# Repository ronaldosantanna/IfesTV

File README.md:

# IfesTV
### Esta Branch é exclusiva do IFES. Os arquivos aqui serão os mesmos da TV presente no IFES.
IfesTV é um site local, no estilo _kiosk_ (Raspberry pi ligado a TV), que exibe videos do youtube, notícias, avisos locais, clima e temperatura ambiente.

> Criado por alunos do IFES - Campus Guarapari. Pelos alunos João Alves, Kevyn Marins e Ronaldo Sant'Anna. [Contato](https://github.com/ronaldosantanna/IfesTV#qualquer-dúvida-ou-sugestão-fiquem-a-vontade)

Utilizamos uma ESP8266 para ligar o sensor local de temperatura DHT11, no qual serve para uma estação remota via comunicalção MQTT com o raspberry pi.
Desse jeito, a raspberry ligada a TV recebe informações de um ou vários sensores em um ou mais prédios e também informações da internet e exibe na TV.

Toda a configuração foi pesquisada na internet e aplicada para este projeto. Aqui tentaremos juntar todas as informações necessárias para a configuração do projeto.

A imagem do sistema já está completa e configurada para uso.

## Hardware
* Raspberry pi 3B + Raspbian [(Img do sistema)](https://drive.google.com/open?id=16IvTq7KXVeJWATDrFhQsSftASu8AablH)
* Esp8266 + [Mosquitto MQTT Server](https://randomnerdtutorials.com/how-to-install-mosquitto-broker-on-raspberry-pi/)
* DHT11

## Configuração do site
O site foi básico apenas para exibir o necessário em nosso projeto. Acima temos os arquivos da página e suas dependencias.
Para editá-lo é simples e qualquer pesquisa na internet já se encontra o passo a passo da criação.

> Para alterar seu conteúdo, por enquanto, temos que acessá-lo remotamente e alterar o valor dentro de seus arquivos de configuração. NO IFES O UNICO LOCAL COM ACESSO REMOTO É A SALA B-307 OU O PRÓPRIO TI.
> 1. Para isso vamos conectar via terminal (pelo linux), ou [Putty](https://the.earth.li/~sgtatham/putty/latest/w32/putty.exe) (windows,   mas teste se seu computador não tem ssh, acessando o cmd e digitando ssh).
 Primeiro devemos descobrir o endereço ip da raspberry. No IFES fixamos o IP dela para 172.17.22.188.
> 2. Conectando pelo hostname fica `ssh pi@172.17.22.188` 
> 3. No terminal digitamos a senha.
 Agora vamos modificar o necessário. Para mudar um arquivo vamos editar pelo editor nano e precisamos ir até o local do arquivo.
> 4. `sudo nano Desktop/IfesTV/JS/script.js`
 Para navegar entre o texto usamos somente as setas do teclado.
> 5. Ao alterar alguma variável e concluirmos as alterações vamos salvar apertando `ctrl + o`. Agora vamos sair apertando `ctrl + x`.
 Para aplicar as mudanças na pagina ela deve ser recarregada. O jeito mais fácil é reiniciando o sistema.
> 6. Para reiniciar (lembre-se de estar conectado via ssh) digitamos `sudo reboot`.

## Configuração da ESP8266
Para configurar a esp é necessário apenas baixar o código da pasta arduino na placa.
O código recebe informações do sensor DHT11 e envia por meio de MQTT para a Raspberry que é um broker, servidor que recebe as informações.

## [_Kiosk Mode_](https://pimylifeup.com/raspberry-pi-kiosk/)

Para Configurar o modo _kiosk_ apenas aplicamos o necessário de alguns tutoriais da internet.

### Qualquer dúvida ou sugestão fiquem a vontade.
Este [formulário](https://forms.gle/AasFBRNRWcPVzgP98) contém um um jeito rápido de contato. Caso se sintam a vontade podem criar um chamado pelo [Issues](https://github.com/ronaldosantanna/IfesTV/issues) do próprio Github.
Ou, caso prefiram deixo meu email para contato: ronaldo.santanna@live.com

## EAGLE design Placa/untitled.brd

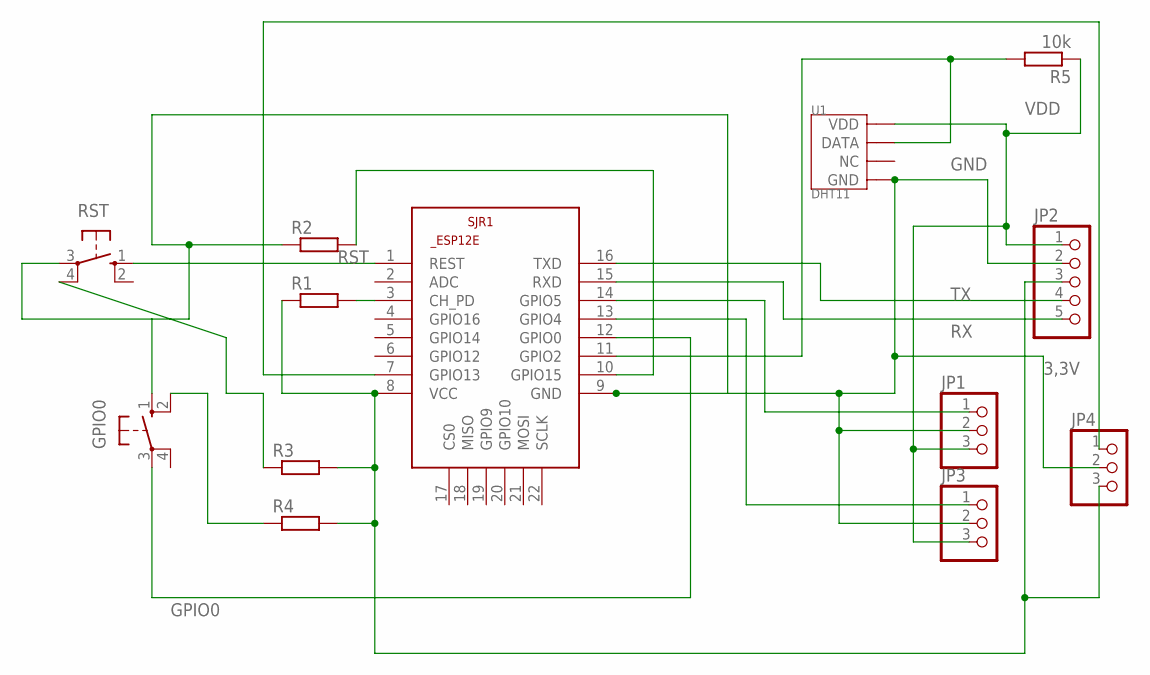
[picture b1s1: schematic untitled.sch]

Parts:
GPIO0: 10-XX; B3F-10XX
JP1, JP3, JP4: PINHD-1X3; 1X03
JP2: PINHD-1X5; 1X05
R1, R2, R3, R4: R-EU_0207/10; 0207/10
R5: 10k; 0207/10
RST: 10-XX; B3F-10XX
SJR1: ESP8266-12EESP12E; ESP8266-ESP12E
U1: DHT11; SNR4-2.54-15.5X12.0X5.5MM

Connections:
3,3V: JP2.3, JP4.3, R1.1, R3.2, R4.2, SJR1.8 (VCC)
GND: GPIO0.1 (S), JP1.2, JP2.2, JP3.2, JP4.2, R2.1, RST.3, SJR1.9 (GND), U1.4 (GND)
GPIO0: GPIO0.3, SJR1.12 (GPIO0)
unnamed: R5.2, SJR1.11 (GPIO2), U1.2 (DATA)
unnamed: R3.1, RST.4 (P1)
unnamed: R1.2, SJR1.3 (CH_PD)
unnamed: R2.2, SJR1.10 (GPIO15)
unnamed: JP1.1, SJR1.14 (GPIO5)
unnamed: JP3.1, SJR1.13 (GPIO4)
unnamed: JP4.1, SJR1.7 (GPIO13)
unnamed: GPIO0.2 (S1), R4.1
RST: RST.1 (S), SJR1.1 (REST)
RX: JP2.5, SJR1.15 (RXD)
TX: JP2.4, SJR1.16 (TXD)
VDD: JP1.3, JP2.1, JP3.3, R5.1, U1.1 (VDD)

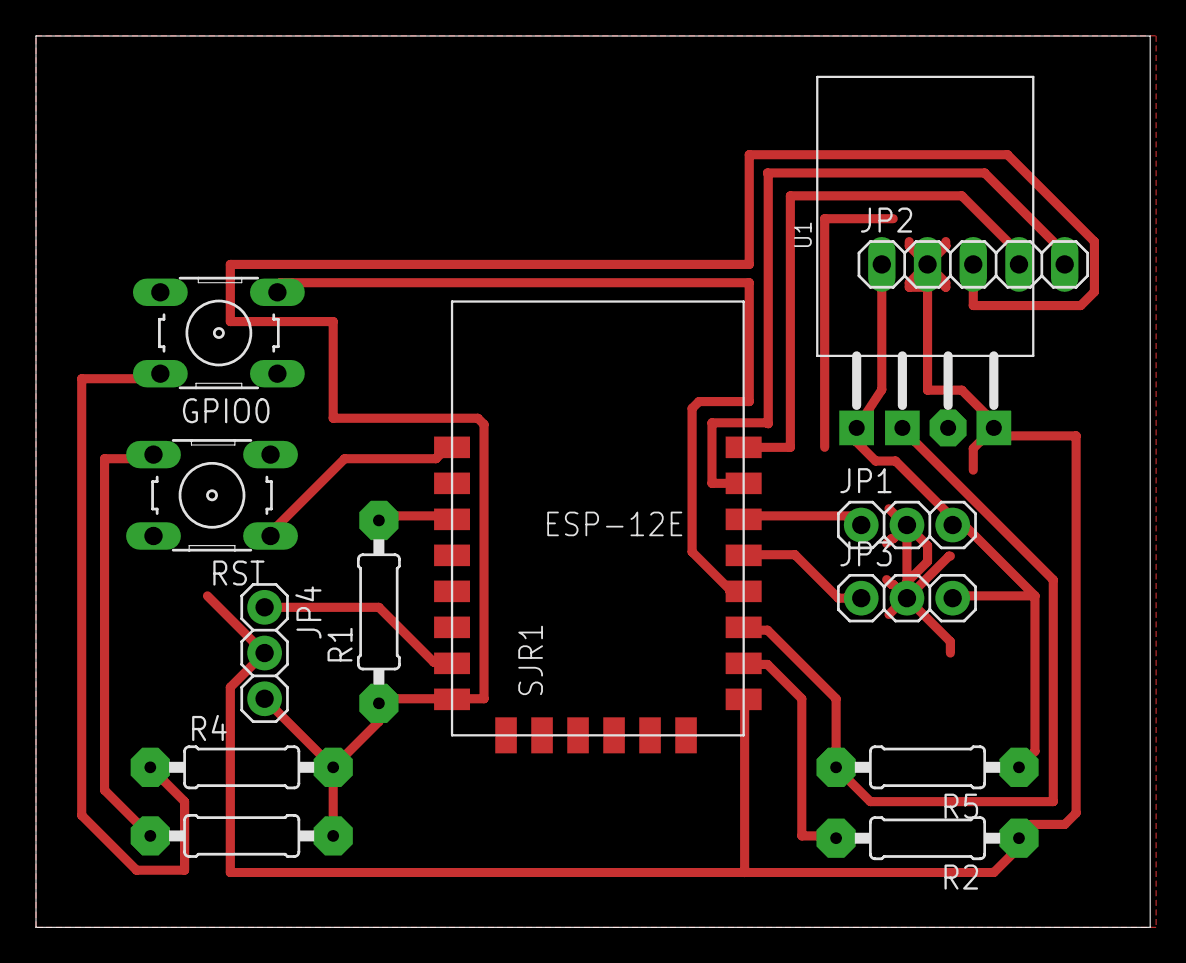
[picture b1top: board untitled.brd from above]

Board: 2 copper layers, 61.9 x 49.5 mm, 13 parts (0 on the bottom side), 15 nets.

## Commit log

2019-06-27 primeiro commit
2019-07-01 Update README.md
    Tutorial inicial.
2019-07-01 Tutorial inicial
    Adicionado descrição e algumas informações de configuração.
2019-07-02 Codigo atualizado
2019-07-03 Adicionado TODO
    Anteriormente: Corrigido erros no texto.
2019-07-03 Adicionado TODO
    Anteriormente: Corrigido erros de digitação.
2019-07-04 codigos finais
2019-07-05 versao final
2019-07-08 Adição do contato.
2019-08-14 Arquivos do IfesTV
2019-08-14 Modificado instruções de acesso pelo IFES
2019-08-14 Alterações visuais
